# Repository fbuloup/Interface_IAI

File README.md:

Please read documentation [here](https://raw.githubusercontent.com/fbuloup/Interface_IAI/main/Documentation/documentation.pdf).

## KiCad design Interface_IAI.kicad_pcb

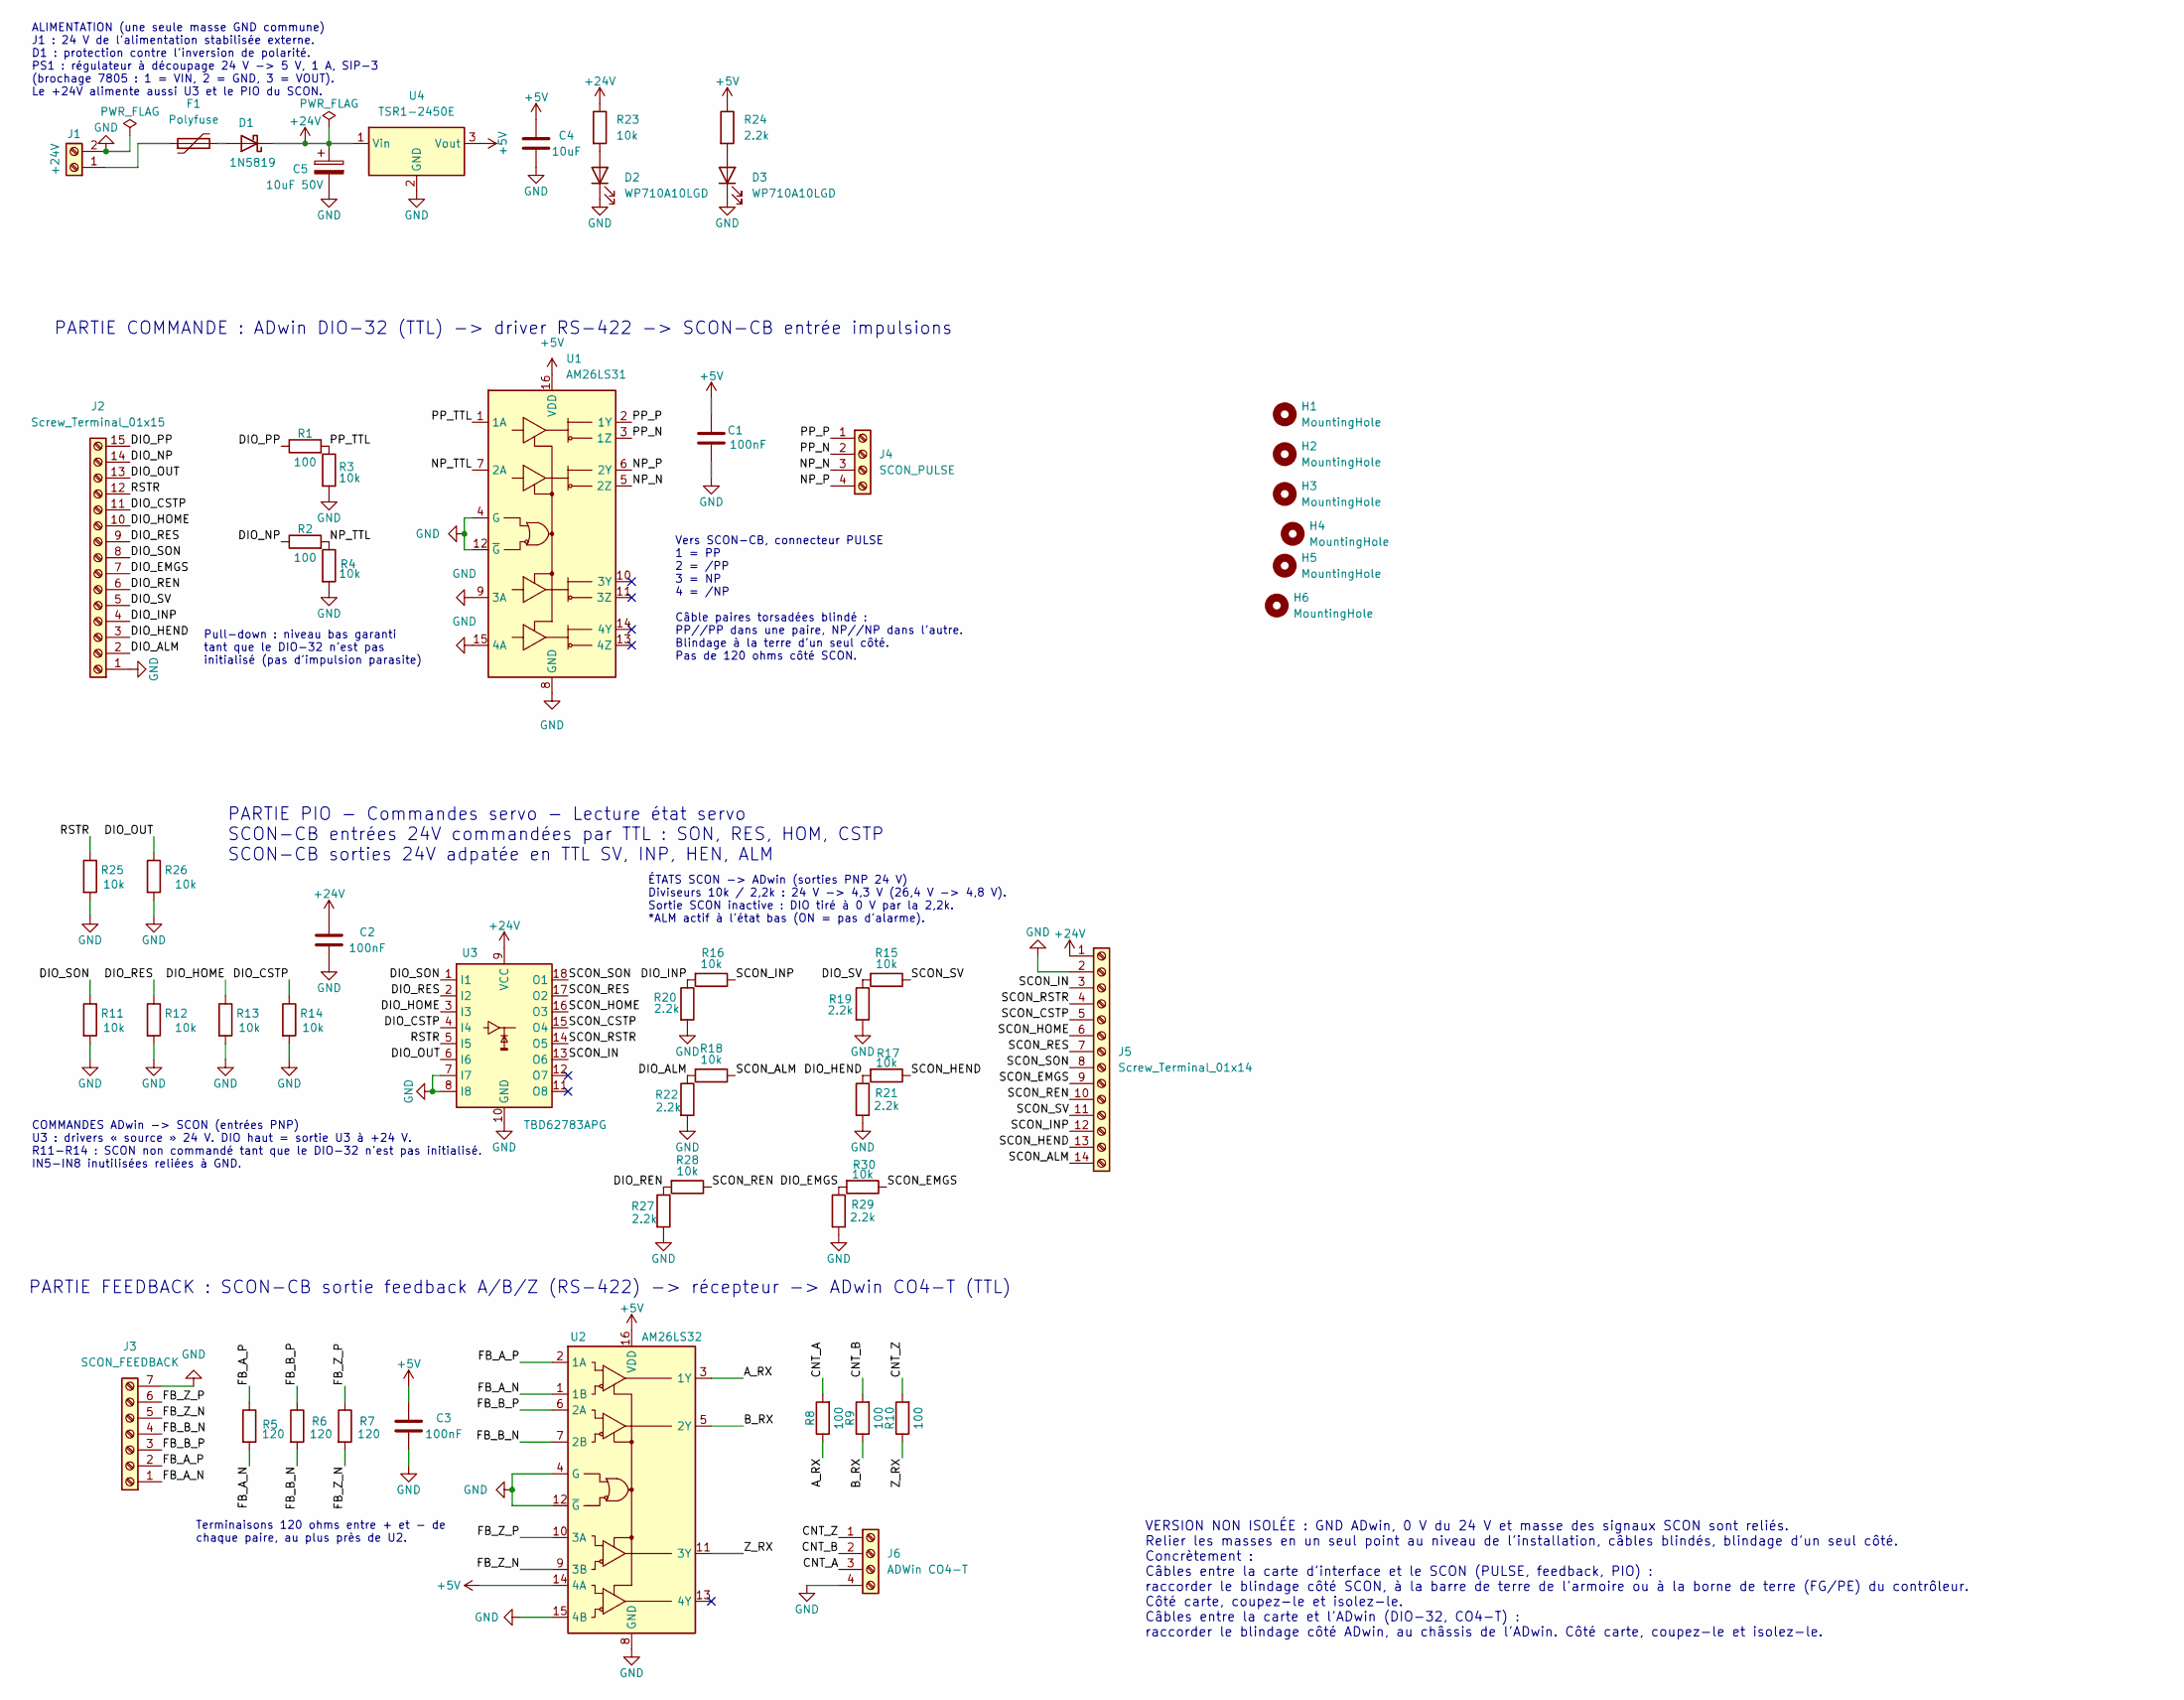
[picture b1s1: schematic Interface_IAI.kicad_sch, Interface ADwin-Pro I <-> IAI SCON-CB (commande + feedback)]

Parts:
C1, C2, C3: 100nF; C_Disc_D5.0mm_W2.5mm_P5.00mm
C4: 10uF; C_Disc_D5.0mm_W2.5mm_P5.00mm
C5: 10uF 50V; CP_Radial_D5.0mm_P2.00mm
D1: 1N5819; D_DO-41_SOD81_P10.16mm_Horizontal
D2, D3: WP710A10LGD; LED_D3.0mm
F1: Polyfuse; MFR050
H1, H2, H3, H4, H5, H6: MountingHole; MountingHole_3.2mm_M3
J1: +24V; TerminalBlock_Phoenix_MKDS-1,5-2-5.08_1x02_P5.08mm_Horizont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
J2: Screw_Terminal_01x15; TerminalBlock_Phoenix_MKDS-1,5-15-5.08_1x15_P5.08mm_Horizon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
J3: SCON_FEEDBACK; TerminalBlock_Phoenix_MKDS-1,5-7-5.08_1x07_P5.08mm_Horizont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
J4: SCON_PULSE; TerminalBlock_Phoenix_MKDS-1,5-4-5.08_1x04_P5.08mm_Horizont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
J5: Screw_Terminal_01x14; TerminalBlock_Phoenix_MKDS-1,5-14-5.08_1x14_P5.08mm_Horizon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
J6: ADWin CO4-T; TerminalBlock_Phoenix_MKDS-1,5-4-5.08_1x04_P5.08mm_Horizont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
R1, R2, R8, R9, R10: 100; R_Axial_DIN0207_L6.3mm_D2.5mm_P7.62mm_Horizontal
R3, R4, R11, R12, R13, R14, R15, R16, R17, R18, R23, R25, R26, R28, R30: 10k; R_Axial_DIN0207_L6.3mm_D2.5mm_P7.62mm_Horizontal
R5, R6, R7: 120; R_Axial_DIN0207_L6.3mm_D2.5mm_P7.62mm_Horizontal
R19, R20, R21, R22, R24, R27, R29: 2.2k; R_Axial_DIN0207_L6.3mm_D2.5mm_P7.62mm_Horizontal
U1: AM26LS31; DIP-16_W7.62mm_Socket
U2: AM26LS32; DIP-16_W7.62mm_Socket
U3: TBD62783APG; DIP-18_W7.62mm_Socket
U4: TSR1-2450E; Converter_DCDC_TRACO_TSR-1_THT

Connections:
+5V: C1.1, C3.1, C4.1, R24.1, U1.16 (VDD), U2.14 (4A), U2.16 (VDD), U4.3 (Vout)
+24V: C2.1, C5.1, D1.1 (K), J5.1, R23.1, U3.9 (VCC), U4.1 (Vin)
/A_RX: R8.1, U2.3 (1Y)
/B_RX: R9.1, U2.5 (2Y)
/CNT_A: J6.3, R8.2
/CNT_B: J6.2, R9.2
/CNT_Z: J6.1, R10.2
/DIO_ALM: J2.2, R18.2, R22.1
/DIO_CSTP: J2.11, R14.1, U3.4 (I4)
/DIO_EMGS: J2.7, R29.1, R30.2
/DIO_HEND: J2.3, R17.2, R21.1
/DIO_HOME: J2.10, R13.1, U3.3 (I3)
/DIO_INP: J2.4, R16.2, R20.1
/DIO_NP: J2.14, R2.1
/DIO_OUT: J2.13, R26.1, U3.6 (I6)
/DIO_PP: J2.15, R1.1
/DIO_REN: J2.6, R27.1, R28.2
/DIO_RES: J2.9, R12.1, U3.2 (I2)
/DIO_SON: J2.8, R11.1, U3.1 (I1)
/DIO_SV: J2.5, R15.2, R19.1
/FB_A_N: J3.1, R5.2, U2.1 (1B)
/FB_A_P: J3.2, R5.1, U2.2 (1A)
/FB_B_N: J3.4, R6.2, U2.7 (2B)
/FB_B_P: J3.3, R6.1, U2.6 (2A)
/FB_Z_N: J3.5, R7.2, U2.9 (3B)
/FB_Z_P: J3.6, R7.1, U2.10 (3A)
/NP_N: J4.3, U1.5 (2Z)
/NP_P: J4.4, U1.6 (2Y)
/NP_TTL: R2.2, R4.1, U1.7 (2A)
/PP_N: J4.2, U1.3 (1Z)
/PP_P: J4.1, U1.2 (1Y)
/PP_TTL: R1.2, R3.1, U1.1 (1A)
/RSTR: J2.12, R25.1, U3.5 (I5)
/SCON_ALM: J5.14, R18.1
/SCON_CSTP: J5.5, U3.15 (O4)
/SCON_EMGS: J5.9, R30.1
/SCON_HEND: J5.13, R17.1
/SCON_HOME: J5.6, U3.16 (O3)
/SCON_IN: J5.3, U3.13 (O6)
/SCON_INP: J5.12, R16.1
/SCON_REN: J5.10, R28.1
/SCON_RES: J5.7, U3.17 (O2)
/SCON_RSTR: J5.4, U3.14 (O5)
/SCON_SON: J5.8, U3.18 (O1)
/SCON_SV: J5.11, R15.1
/Z_RX: R10.1, U2.11 (3Y)
GND: C1.2, C2.2, C3.2, C4.2, C5.2, D2.1 (K), D3.1 (K), J1.2, J2.1, J3.7, J5.2, J6.4, R3.2, R4.2, R11.2, R12.2, R13.2, R14.2, R19.2, R20.2, R21.2, R22.2, R25.2, R26.2, R27.2, R29.2, U1.4 (G), U1.8 (GND), U1.9 (3A), U1.12 (~G), U1.15 (4A), U2.4 (G), U2.8 (GND), U2.12 (~G), U2.15 (4B), U3.7 (I7), U3.8 (I8), U3.10 (GND), U4.2 (GND)
unnamed: D1.2 (A), F1.2
unnamed: D2.2 (A), R23.2
unnamed: D3.2 (A), R24.2
unnamed: F1.1, J1.1

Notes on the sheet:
COMMANDES ADwin -> SCON (entrées PNP) U3 : drivers « source » 24 V. DIO haut = sortie U3 à +24 V. R11-R14 : SCON non commandé tant que le DIO-32 n'est pas initialisé. IN5-IN8 inutilisées reliées à GND.
ÉTATS SCON -> ADwin (sorties PNP 24 V) Diviseurs 10k / 2,2k : 24 V -> 4,3 V (26,4 V -> 4,8 V). Sortie SCON inactive : DIO tiré à 0 V par la 2,2k. *ALM actif à l'état bas (ON = pas d'alarme).
Vers SCON-CB, connecteur PULSE 1 = PP 2 = /PP 3 = NP 4 = /NP Câble paires torsadées blindé : PP//PP dans une paire, NP//NP dans l'autre. Blindage à la terre d'un seul côté. Pas de 120 ohms côté SCON.
Pull-down : niveau bas garanti tant que le DIO-32 n'est pas initialisé (pas d'impulsion parasite)
Terminaisons 120 ohms entre + et - de chaque paire, au plus près de U2.
PARTIE FEEDBACK : SCON-CB sortie feedback A/B/Z (RS-422) -> récepteur -> ADwin CO4-T (TTL)
PARTIE PIO - Commandes servo - Lecture état servo SCON-CB entrées 24V commandées par TTL : SON, RES, HOM, CSTP SCON-CB sorties 24V adpatée en TTL SV, INP, HEN, ALM
ALIMENTATION (une seule masse GND commune) J1 : 24 V de l'alimentation stabilisée externe. D1 : protection contre l'inversion de polarité. PS1 : régulateur à découpage 24 V -> 5 V, 1 A, SIP-3 (brochage 7805 : 1 = VIN, 2 = GND, 3 = VOUT). Le +24V alimente aussi U3 et le PIO du SCON.
PARTIE COMMANDE : ADwin DIO-32 (TTL) -> driver RS-422 -> SCON-CB entrée impulsions
VERSION NON ISOLÉE : GND ADwin, 0 V du 24 V et masse des signaux SCON sont reliés. Relier les masses en un seul point au niveau de l'installation, câbles blindés, blindage d'un seul côté. Concrètement : Câbles entre la carte d'interface et le SCON (PULSE, feedback, PIO) : raccorder le blindage côté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

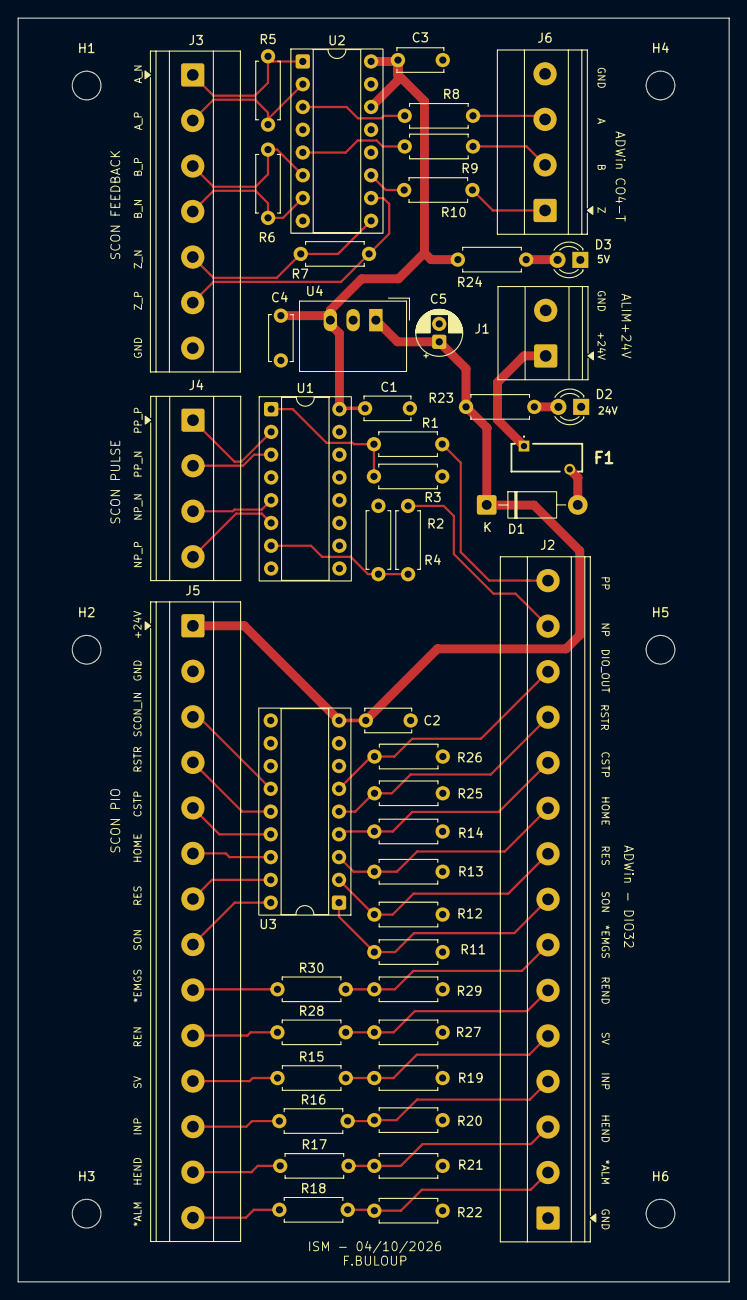
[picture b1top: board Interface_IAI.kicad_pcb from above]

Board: 2 copper layers, 79.3 x 141.0 mm, 55 parts (0 on the bottom side), 51 nets.
